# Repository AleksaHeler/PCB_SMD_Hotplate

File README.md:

# PCB_SMD_Hotplate
 A DIY approach to a hotplate to assemble SMD components on the PCB, using ATMega328 MCU, Solid State Relay and a thermocouple.

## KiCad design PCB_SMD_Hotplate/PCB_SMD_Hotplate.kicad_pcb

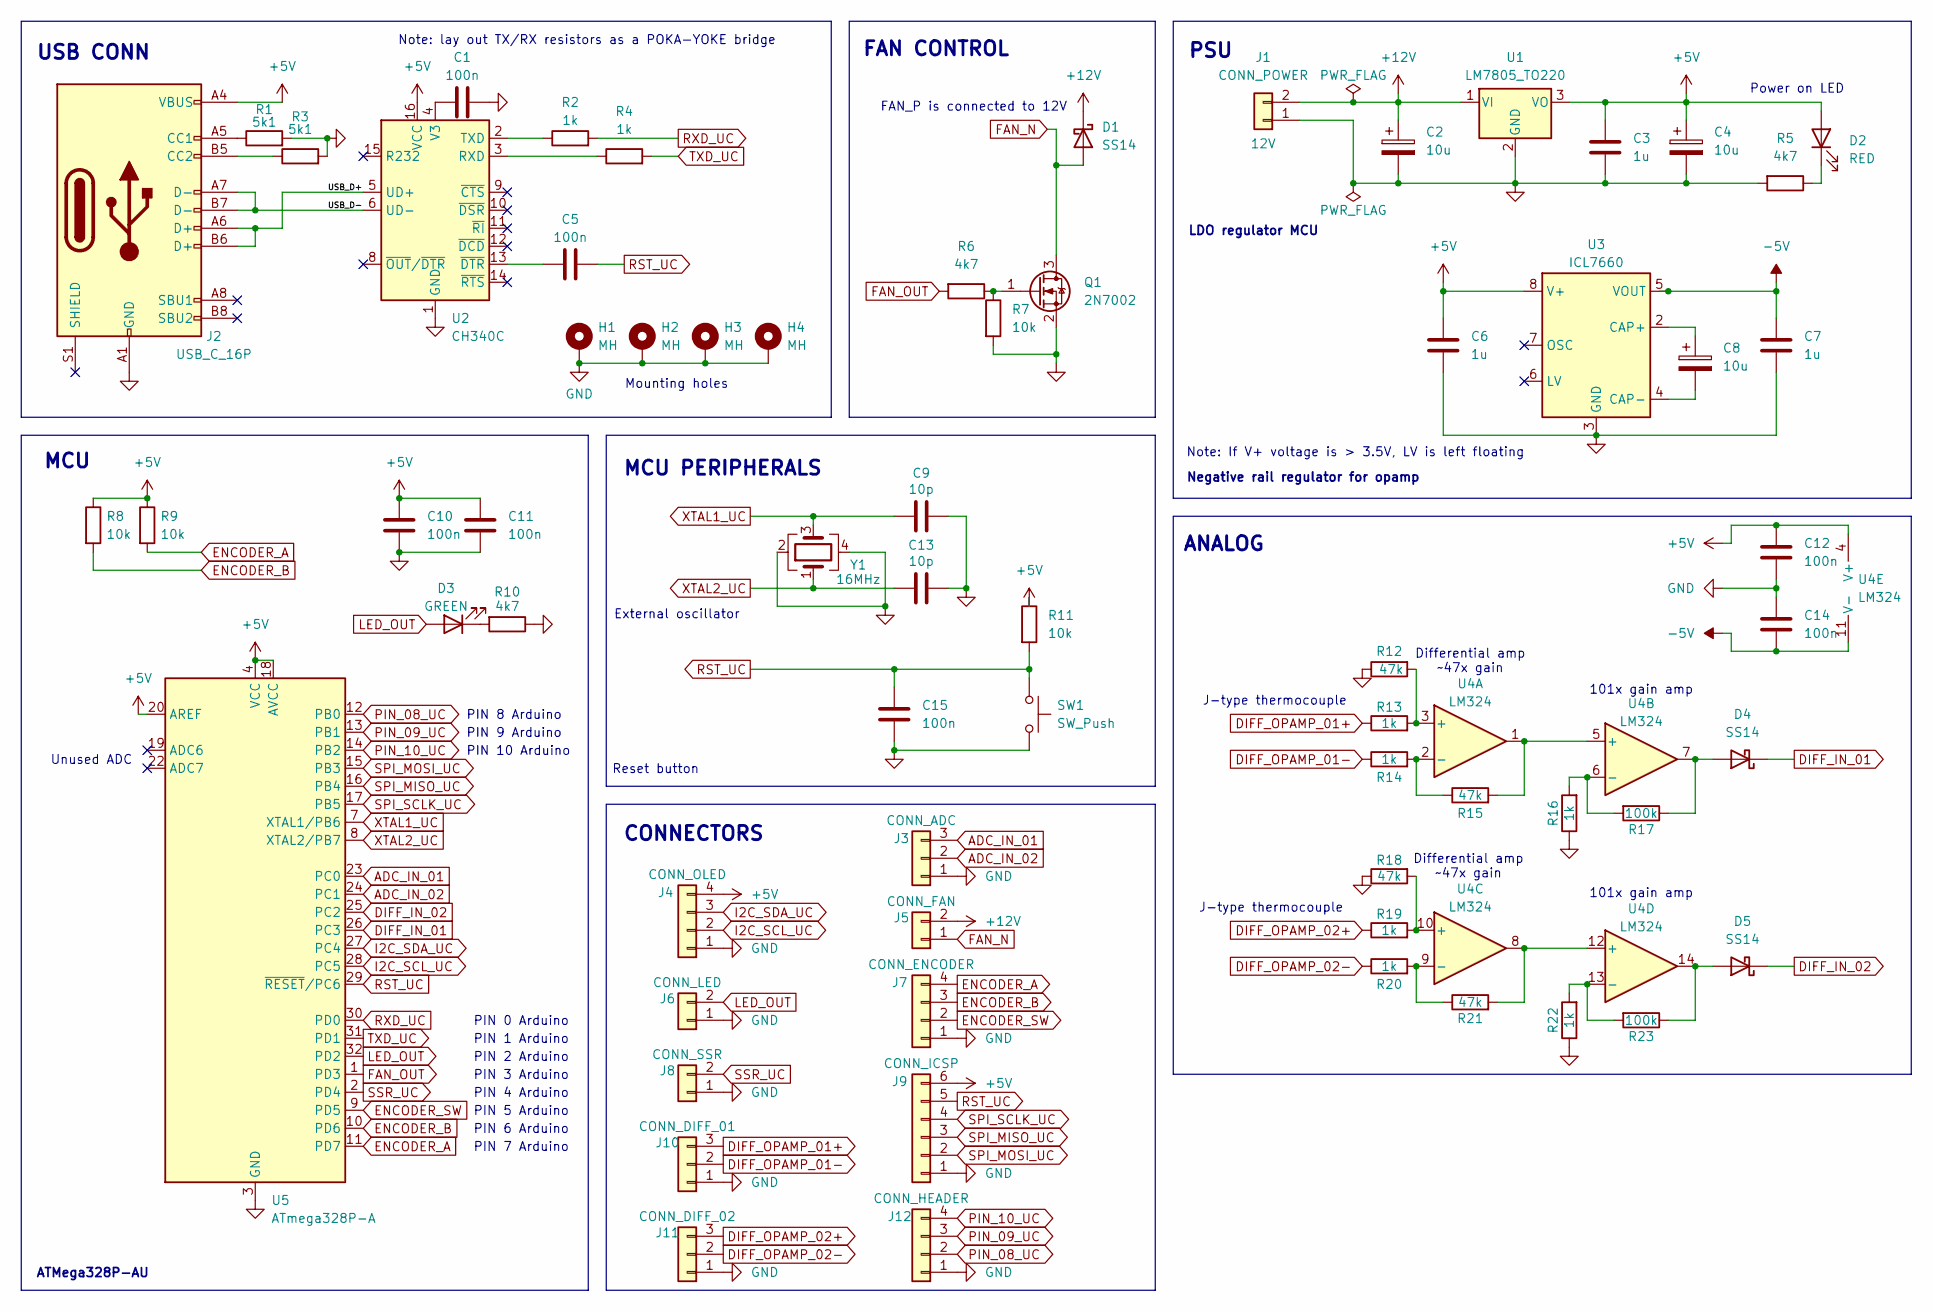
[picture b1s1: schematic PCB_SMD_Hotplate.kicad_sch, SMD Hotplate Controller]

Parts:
C1, C5, C10, C11, C12, C14, C15: 100n; C_0805_2012Metric
C2, C4, C8: 10u; CP_Elec_6.3x7.7
C3, C6, C7: 1u; C_0805_2012Metric
C9, C13: 10p; C_0805_2012Metric
D1, D4, D5: SS14; D_SMA
D2: RED; LED_1210_3225Metric
D3: GREEN; LED_1210_3225Metric
H1, H2, H3, H4: MH; MountingHole_3.2mm_M3_Pad_Via
J1: CONN_POWER; PinHeader_1x02_P2.54mm_Vertical; Voltage 12V
J2: USB_C_16P; USB_C_Receptacle_G-Switch_GT-USB-7010ASV
J3: CONN_ADC; PinHeader_1x03_P2.54mm_Vertical
J4: CONN_OLED; PinHeader_1x04_P2.54mm_Vertical
J5: CONN_FAN; PinHeader_1x02_P2.54mm_Vertical
J6: CONN_LED; PinHeader_1x02_P2.54mm_Vertical
J7: CONN_ENCODER; PinHeader_1x04_P2.54mm_Vertical
J8: CONN_SSR; PinHeader_1x02_P2.54mm_Vertical
J9: CONN_ICSP; PinHeader_1x06_P2.54mm_Vertical
J10: CONN_DIFF_01; PinHeader_1x03_P2.54mm_Vertical
J11: CONN_DIFF_02; PinHeader_1x03_P2.54mm_Vertical
J12: CONN_HEADER; PinHeader_1x04_P2.54mm_Vertical
Q1: 2N7002; SOT-23
R1, R3: 5k1; R_0805_2012Metric
R2, R4, R13, R14, R16, R19, R20, R22: 1k; R_0805_2012Metric
R5, R6, R10: 4k7; R_0805_2012Metric
R7, R8, R9, R11: 10k; R_0805_2012Metric
R12, R15, R18, R21: 47k; R_0805_2012Metric
R17, R23: 100k; R_0805_2012Metric
SW1: SW_Push; SW_PUSH_6mm_H4.3mm
U1: LM7805_TO220; TO-220-3_Vertical
U2: CH340C; SOIC-16_3.9x9.9mm_P1.27mm
U3: ICL7660; MSOP-8_3x3mm_P0.65mm
U4: LM324; SOIC-14_3.9x8.7mm_P1.27mm
U5: ATmega328P-A; TQFP-32_7x7mm_P0.8mm
Y1: 16MHz; Crystal_SMD_3225-4Pin_3.2x2.5mm

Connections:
+5V: C3.1, C4.1, C6.1, C10.1, C11.1, C12.1, D2.2 (A), J2.A4 (VBUS), J2.A9 (VBUS), J2.B4 (VBUS), J2.B9 (VBUS), J4.4, J9.6, R8.1, R9.1, R11.1, U1.3 (VO), U2.16 (VCC), U3.8 (V+), U4.4 (V+), U5.4 (VCC), U5.6 (VCC), U5.18 (AVCC), U5.20 (AREF)
+12V: C2.1, D1.1 (K), J1.2, J5.2, U1.1 (VI)
-5V: C7.1, C14.2, U3.5 (VOUT), U4.11 (V-)
/USB_D+: J2.A6 (D+), J2.B6 (D+), U2.5 (UD+)
/USB_D-: J2.A7 (D-), J2.B7 (D-), U2.6 (UD-)
ADC_IN_01: J3.3, U5.23 (PC0)
ADC_IN_02: J3.2, U5.24 (PC1)
DIFF_IN_01: D4.1 (K), U5.26 (PC3)
DIFF_IN_02: D5.1 (K), U5.25 (PC2)
DIFF_OPAMP_01+: J10.3, R13.1
DIFF_OPAMP_01-: J10.2, R14.1
DIFF_OPAMP_02+: J11.3, R19.1
DIFF_OPAMP_02-: J11.2, R20.1
ENCODER_A: J7.4, R9.2, U5.11 (PD7)
ENCODER_B: J7.3, R8.2, U5.10 (PD6)
ENCODER_SW: J7.2, U5.9 (PD5)
FAN_N: D1.2 (A), J5.1, Q1.3 (D)
FAN_OUT: R6.2, U5.1 (PD3)
GND: C1.2, C2.2, C3.2, C4.2, C6.2, C7.2, C9.1, C10.2, C11.2, C12.2, C13.1, C14.1, C15.2, H1.1, H2.1, H3.1, H4.1, J1.1, J2.A1 (GND), J2.A12 (GND), J2.B1 (GND), J2.B12 (GND), J3.1, J4.1, J6.1, J7.1, J8.1, J9.1, J10.1, J11.1, J12.1, Q1.2 (S), R1.2, R3.2, R5.2, R7.2, R10.1, R12.1, R16.1, R18.1, R22.1, SW1.2, U1.2 (GND), U2.1 (GND), U3.3 (GND), U5.3 (GND), U5.5 (GND), U5.21 (GND), Y1.2, Y1.4
I2C_SCL_UC: J4.2, U5.28 (PC5)
I2C_SDA_UC: J4.3, U5.27 (PC4)
LED_OUT: D3.2 (A), J6.2, U5.32 (PD2)
unnamed: D2.1 (K), R5.1
unnamed: D3.1 (K), R10.2
unnamed: D4.2 (A), R17.1, U4.7
unnamed: D5.2 (A), R23.1, U4.14
unnamed: J2.A5 (CC1), R1.1
unnamed: J2.B5 (CC2), R3.1
unnamed: Q1.1 (G), R6.1, R7.1
unnamed: R4.1, U2.3 (RXD)
unnamed: R2.1, U2.2 (TXD)
unnamed: C1.1, U2.4 (V3)
unnamed: C5.1, U2.13 (~DTR)
unnamed: C8.1, U3.2 (CAP+)
unnamed: C8.2, U3.4 (CAP-)
unnamed: R12.2, R13.2, U4.3 (+)
unnamed: R14.2, R15.1, U4.2 (-)
unnamed: R15.2, U4.1, U4.5 (+)
unnamed: R16.2, R17.2, U4.6 (-)
unnamed: R18.2, R19.2, U4.10 (+)
unnamed: R20.2, R21.1, U4.9 (-)
unnamed: R21.2, U4.8, U4.12 (+)
unnamed: R22.2, R23.2, U4.13 (-)
PIN_08_UC: J12.2, U5.12 (PB0)
PIN_09_UC: J12.3, U5.13 (PB1)
PIN_10_UC: J12.4, U5.14 (PB2)
RST_UC: C5.2, C15.1, J9.5, R11.2, SW1.1, U5.29 (~RESET/PC6)
RXD_UC: R2.2, U5.30 (PD0)
SPI_MISO_UC: J9.3, U5.16 (PB4)
SPI_MOSI_UC: J9.2, U5.15 (PB3)
SPI_SCLK_UC: J9.4, U5.17 (PB5)
SSR_UC: J8.2, U5.2 (PD4)
TXD_UC: R4.2, U5.31 (PD1)
XTAL1_UC: C9.2, U5.7 (XTAL1/PB6), Y1.3
XTAL2_UC: C13.2, U5.8 (XTAL2/PB7), Y1.1

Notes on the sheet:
Differential amp ~47x gain
Negative rail regulator for opamp
PIN 7 Arduino
Note: If V+ voltage is > 3.5V, LV is left floating
CONNECTORS
PIN 10 Arduino
ATMega328P-AU
Note: lay out TX/RX resistors as a POKA-YOKE bridge
PIN 6 Arduino
J-type thermocouple
LDO regulator MCU
PIN 5 Arduino
MCU PERIPHERALS
ANALOG
PIN 1 Arduino
Power on LED
PIN 8 Arduino
PIN 2 Arduino
PSU
USB CONN
PIN 9 Arduino
Reset button
FAN CONTROL
Mounting holes
101x gain amp
PIN 3 Arduino
External oscillator
MCU
PIN 0 Arduino
PIN 4 Arduino
Unused ADC
FAN_P is connected to 12V

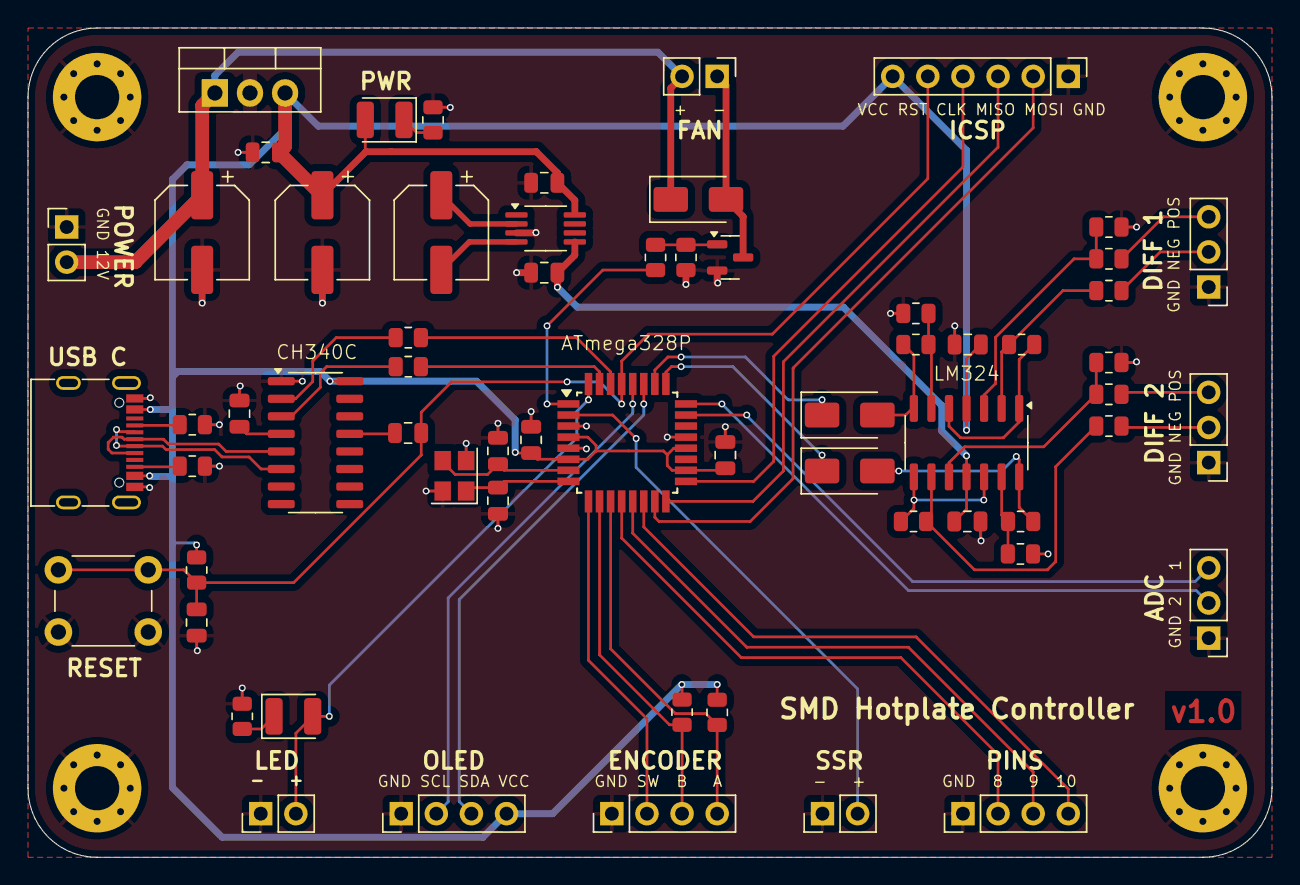
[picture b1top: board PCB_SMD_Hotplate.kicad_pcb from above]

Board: 2 copper layers, 90.0 x 60.0 mm, 67 parts (0 on the bottom side), 55 nets.

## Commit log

2024-04-25 Create basic KiCAD project
2024-04-27 Update schematic, start PCB
2024-04-28 Finish schm, finish component layout
2024-04-28 Finish layout and routing
2024-05-02 Finish PCB and prepare files for ordering
